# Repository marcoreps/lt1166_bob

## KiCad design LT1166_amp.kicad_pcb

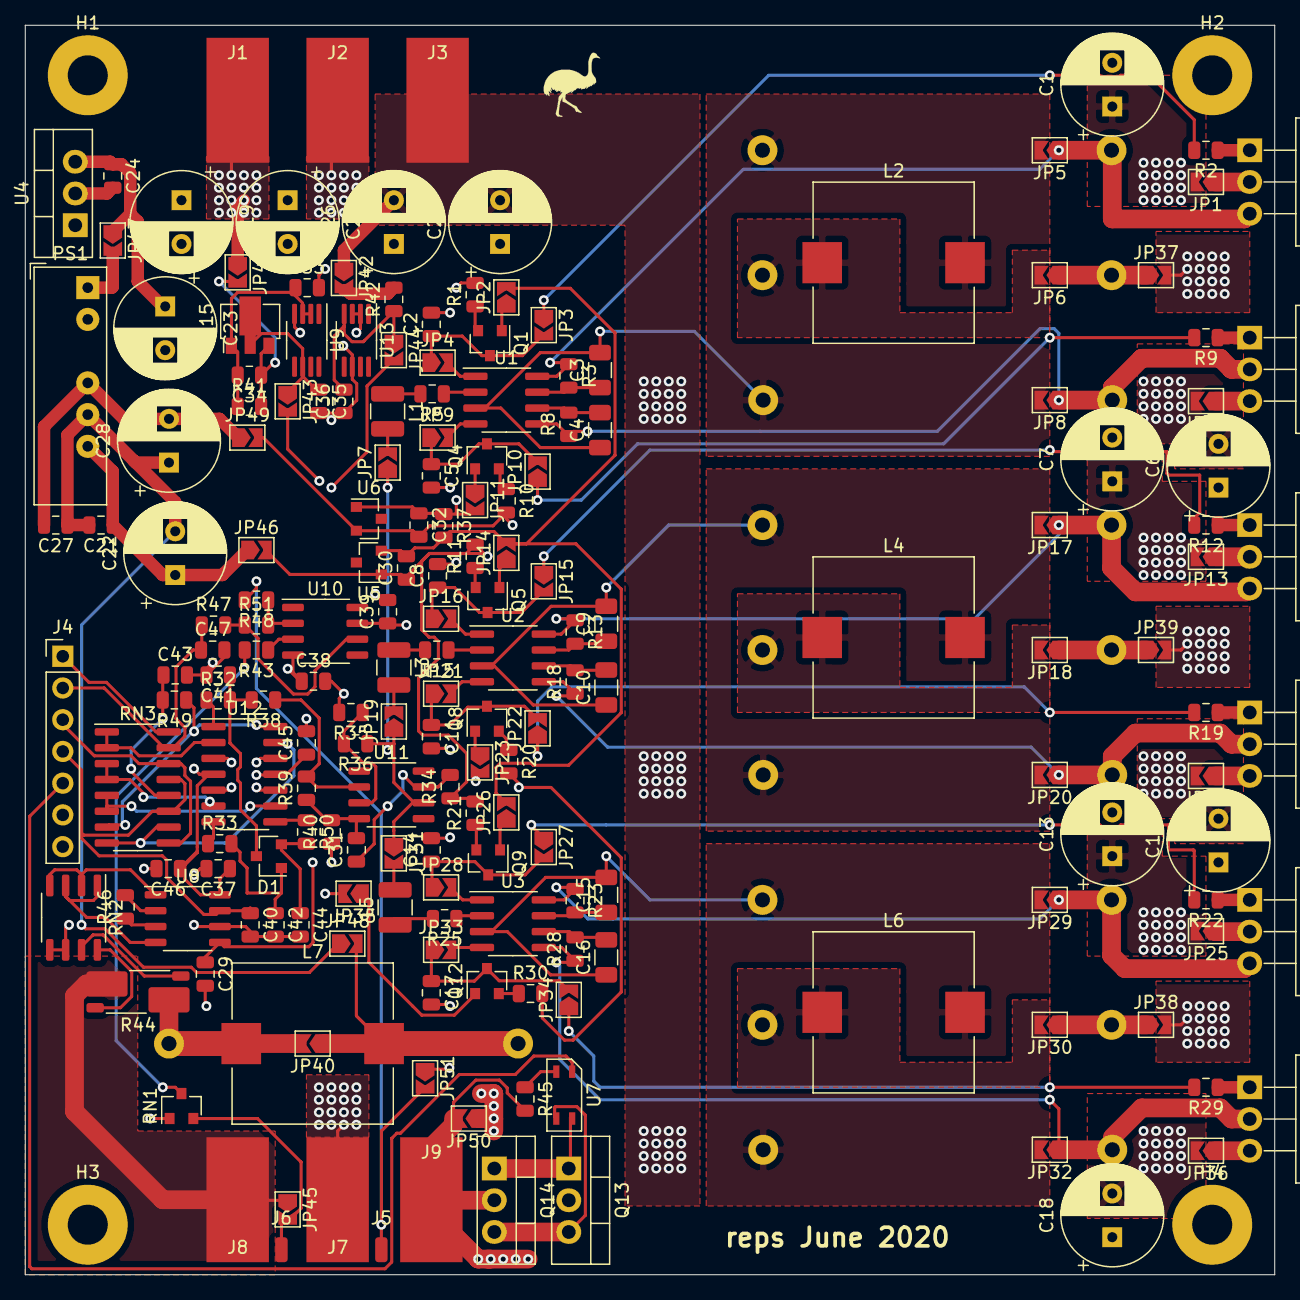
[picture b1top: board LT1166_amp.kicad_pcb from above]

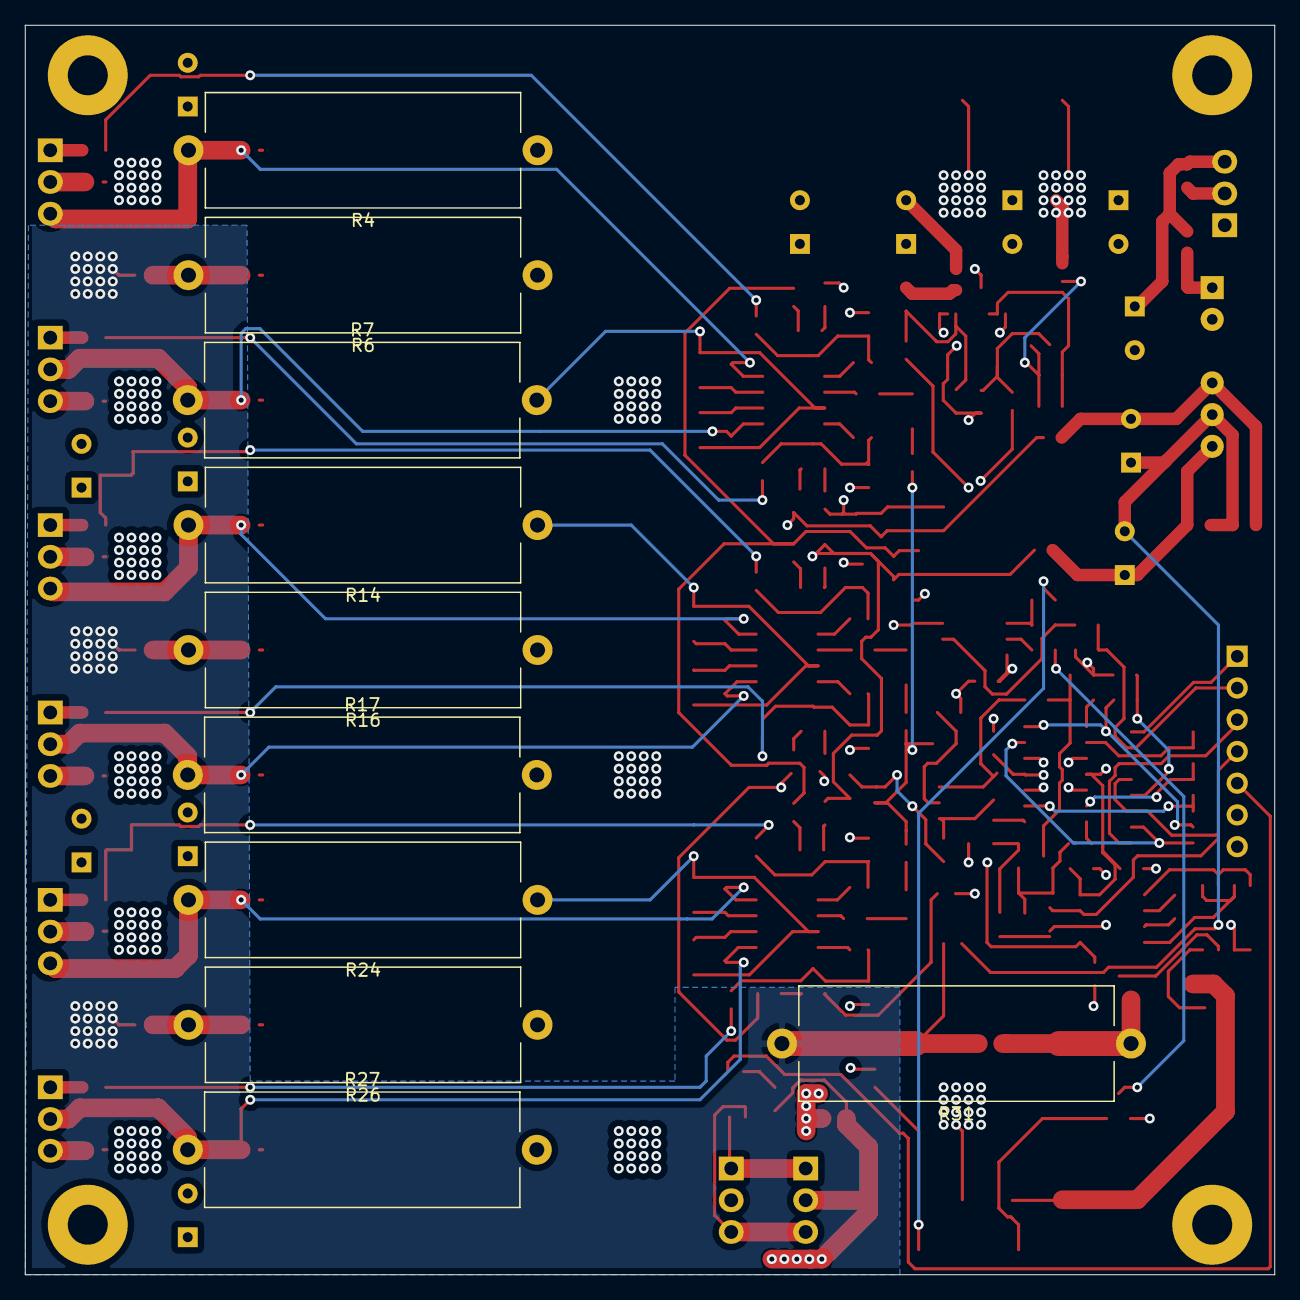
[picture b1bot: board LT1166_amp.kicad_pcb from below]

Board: 4 copper layers, 100.0 x 100.0 mm, 202 parts (10 on the bottom side), 132 nets.

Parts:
C1, C6, C7, C12, C13, C18, C19, C20, C25, C26: 1000µF; CP_Radial_D8.0mm_P3.50mm
C2, C5, C8, C11, C14, C17: 1nF; C_0805_2012Metric
C3, C4, C9, C10, C15, C16: 1µF; C_1206_3216Metric
C21, C24, C27, C29, C31, C33, C37, C38, C39, C45, C46: 100nF; C_0805_2012Metric
C22, C23, C28: 220µF; CP_Radial_D8.0mm_P3.50mm
C30, C32: 10µF; C_0805_2012Metric
C34: 4.7µF; C_0805_2012Metric
C35, C36: 1µF; C_0805_2012Metric
C40, C41, C42, C43, C44, C47: 0nF; C_0805_2012Metric
D1: D_Schottky_x2_Serial_AKC; SOT-23
H1, H2, H3, H4: MountingHole_Pad; MountingHole_3.2mm_M3_Pad
J1, J2, J3: Conn_01x01; SolderWirePad_1x01_SMD_5x10mm
J4: Conn_01x07; PinHeader_1x07_P2.54mm_Vertical
J5: sense-r; SolderWirePad_1x01_SMD_1x2mm
J6: sense-f; SolderWirePad_1x01_SMD_1x2mm
J7: return; SolderWirePad_1x01_SMD_5x10mm
J8: force; SolderWirePad_1x01_SMD_5x10mm
J9: PE; SolderWirePad_1x01_SMD_5x10mm
JP1, JP2, JP3, JP4, JP5, JP6, JP7, JP8, JP9, JP10, JP11, JP12, JP13, JP14, JP15, JP16, JP17, JP18, JP19, JP20, JP21, JP22, JP23, JP24, JP25, JP26, JP27, JP28, JP29, JP30, JP31, JP32, JP33, JP34, JP35, JP36, JP37, JP38, JP39, JP40, JP41, JP42, JP43, JP44, JP45, JP46, JP47, JP48, JP49, JP50, JP51: Jumper_NC_Small; SolderJumper-2_P1.3mm_Open_TrianglePad1.0x1.5mm
L1, L3, L5: 180µH; L_1210_3225Metric
L2, L4, L6: 0.4µH; L_Vishay_IHLP-5050
L7: 1.5µH; L_Vishay_IHLP-5050
PS1: IA2415S; Converter_DCDC_XP_POWER-IAxxxxS_THT
Q1, Q5, Q9: Q_PNP_BEC; SOT-23
Q2, Q6, Q10: IRF540N; TO-220-3_Horizontal_TabDown
Q3, Q7, Q11: IRF9540N; TO-220-3_Horizontal_TabDown
Q4, Q8, Q12: Q_NPN_BEC; SOT-23
Q13, Q14: Q_NMOS_GDS; TO-220-3_Vertical
Q15: Q_PNP_BCE; SOT-89-3
R1, R2, R9, R10, R11, R12, R19, R20, R21, R22, R29, R30: 100R; R_0805_2012Metric
R3, R8, R13, R18, R23, R28: 1k; R_0805_2012Metric
R4, R6, R7, R14, R16, R17, R24, R26, R27: 0.33R; R_Axial_Power_L25.0mm_W9.0mm_P27.94mm
R5, R15, R25: 2k; R_0805_2012Metric
R31: 1R; R_Axial_Power_L25.0mm_W9.0mm_P27.94mm
R32, R38: 10kOhm; R_0805_2012Metric
R33, R43, R47, R48, R49, R50, R51: 0Ohm; R_0805_2012Metric
R34, R40: 390Ohm; R_0805_2012Metric
R35: 9.1kOhm; R_0805_2012Metric
R36, R37, R39: 1kOhm; R_0805_2012Metric
R41: 220Ohm; R_0805_2012Metric
R42: 4kOhm; R_0805_2012Metric
R44: 10mOhm; R_Shunt_Vishay_WSK2512_6332Metric_T2.21mm
R45: 250Ohm; R_0805_2012Metric
R46: 316Ohm; R_0805_2012Metric
RN1: MPM; SOT-23
RN2: 10:1; SO-8_3.9x4.9mm_P1.27mm
RN3: R_Pack08_Split; SOIC-16_3.9x9.9mm_P1.27mm
U1, U2, U3: LT1166; SOIC-8_3.9x4.9mm_P1.27mm
U4: L7824; TO-220-3_Vertical
U5, U6: LM4040DBZ-2.5; SOT-23
U7: TLP3914; SSOP-4
U8: AD8429; SO-8_3.9x4.9mm_P1.27mm
U9, U13: LT6657BHMS8-5; MSOP-8_3x3mm_P0.65mm
U10, U11: LT1360; SO-8_3.9x4.9mm_P1.27mm
U12: Opamp_Quad_Generic; SOIC-14_3.9x8.7mm_P1.27mm

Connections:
+5V: C37.1, C39.1, C46.1, JP43.2, U8.8, U10.7, U12.4
+15VF: C30.1, JP46.2, R1.2, R11.2, R21.2, R34.1, U5.1
+24V: C23.1, C24.1, JP47.1, U4.3
+VDC: C1.1, C7.1, C13.1, C19.1, C20.1, J1.1, JP1.2, JP13.2, JP25.2, JP41.1, U4.1
-5V: C29.1, C38.1, C45.1, JP44.2, U8.5, U10.4, U12.11
-15VF: C32.2, JP49.2, R10.2, R20.2, R30.2, R40.1, U6.2
-VDC: C6.2, C12.2, C18.2, C25.2, C26.2, J3.1, JP12.2, JP24.2, JP36.2, JP42.1
/Output and feedback/I_fb: C40.1, J4.4, RN3.11, RN3.13, U8.7
/Output and feedback/PE_ssr: J4.5, U7.1
/Output and feedback/V_fb: C47.1, J4.2, R47.1, RN3.15
/Output and feedback/in: JP40.2, L7.1, R31.1, R44.1
/Power slice 1/in: JP7.1, JP19.1, JP31.1, R36.1, U11.6
/V I clamp/I_set: J4.3, RN3.9, RN3.14
/V I clamp/V_set: J4.1, RN3.16
GND: C1.2, C2.2, C5.2, C6.1, C7.2, C8.2, C11.2, C12.1, C13.2, C14.2, C17.2, C18.1, C19.2, C20.2, C23.2, C24.2, C25.1, C26.1, C29.2, C33.2, C35.2, C36.1, C37.2, C38.2, C39.2, C40.2, C41.2, C42.2, C43.2, C44.2, C45.2, C46.2, C47.2, J2.1, J4.6, J7.1, JP50.1, JP51.1, PS1.2, Q13.2, R35.2, RN1.1, RN2.5, RN2.6, U4.2, U8.6, U9.4, U12.3, U12.5, U12.10, U12.12, U13.2, U13.3, U13.6
unnamed: C2.1, JP3.2, JP4.1, Q1.3
unnamed: C3.1, R3.2, U1.7
unnamed: C3.2, C4.1, JP5.2, JP8.2, L2.2, R4.1, R7.2, U1.3
unnamed: C4.2, R8.2, U1.6
unnamed: C5.1, JP9.1, JP10.2, Q4.3
unnamed: C8.1, JP15.2, JP16.1, Q5.3
unnamed: C9.1, R13.2, U2.7
unnamed: C9.2, C10.1, JP17.2, JP20.2, L4.2, R14.1, R17.2, U2.3
unnamed: C10.2, R18.2, U2.6
unnamed: C11.1, JP21.1, JP22.2, Q8.3
unnamed: C14.1, JP27.2, JP28.1, Q9.3
unnamed: C15.1, R23.2, U3.7
unnamed: C15.2, C16.1, JP29.2, JP32.2, L6.2, R24.1, R27.2, U3.3
unnamed: C16.2, R28.2, U3.6
unnamed: C17.1, JP33.1, JP34.2, Q12.3
unnamed: C21.1, C22.1, JP46.1, PS1.6
unnamed: C21.2, C22.2, C27.1, C28.1, JP48.1, PS1.5
unnamed: C27.2, C28.2, JP49.1, PS1.4
unnamed: C31.1, R34.2, U11.7
unnamed: C31.2, R39.1, R40.2, U11.4
unnamed: C33.1, C34.2, Q15.1, R41.1, U9.2, U9.3
unnamed: C34.1, JP41.2, Q15.3, R41.2
unnamed: C35.1, JP43.1, Q15.2, U9.6
unnamed: C36.2, JP44.1, R42.1, U13.4
unnamed: C42.1, D1.1, R33.2
unnamed: C43.1, R49.2, RN3.12
unnamed: C44.1, D1.2, R50.2
unnamed: J5.1, JP51.2, R48.2
unnamed: J6.1, JP45.2, RN1.2
unnamed: J8.1, JP45.1, R44.4
unnamed: JP1.1, Q2.2
unnamed: JP2.1, Q1.1
unnamed: JP3.1, R2.2
unnamed: JP4.2, U1.1
unnamed: JP5.1, Q2.3, R3.1, R4.2, U1.8
unnamed: JP6.2, L2.1, R6.1
unnamed: JP7.2, L1.2
unnamed: JP8.1, Q3.2, R7.1, R8.1, U1.5
unnamed: JP9.2, U1.4
unnamed: JP10.1, R9.2
unnamed: JP11.1, Q4.1
unnamed: JP12.1, Q3.3
unnamed: JP13.1, Q6.2
unnamed: JP14.1, Q5.1
unnamed: JP15.1, R12.2
unnamed: JP16.2, U2.1
unnamed: JP17.1, Q6.3, R13.1, R14.2, U2.8
unnamed: JP18.1, JP39.1, R16.2
unnamed: JP18.2, L4.1, R16.1
unnamed: JP19.2, L3.2
unnamed: JP20.1, Q7.2, R17.1, R18.1, U2.5
unnamed: JP21.2, U2.4
unnamed: JP22.1, R19.2
unnamed: JP23.1, Q8.1
unnamed: JP24.1, Q7.3
unnamed: JP25.1, Q10.2
unnamed: JP26.1, Q9.1
unnamed: JP27.1, R22.2
unnamed: JP28.2, U3.1
unnamed: JP29.1, Q10.3, R23.1, R24.2, U3.8
unnamed: JP30.1, JP38.1, R26.2
unnamed: JP30.2, L6.1, R26.1
unnamed: JP31.2, L5.2
unnamed: JP32.1, Q11.2, R27.1, R28.1, U3.5
unnamed: JP33.2, U3.4
unnamed: JP34.1, R29.2
unnamed: JP35.1, Q12.1
unnamed: JP36.1, Q11.3
unnamed: JP6.1, JP37.1, R6.2
unnamed: JP42.2, R42.2
unnamed: JP47.2, PS1.1
unnamed: L1.1, R5.2
unnamed: L3.1, R15.2
unnamed: L5.1, R25.2
unnamed: Q1.2, R1.1
unnamed: Q2.1, R2.1
unnamed: Q3.1, R9.1
unnamed: Q4.2, R10.1
unnamed: Q5.2, R11.1
unnamed: Q6.1, R12.1
unnamed: Q7.1, R19.1
unnamed: Q8.2, R20.1
unnamed: Q9.2, R21.1
unnamed: Q10.1, R22.1
unnamed: Q11.1, R29.1
unnamed: Q12.2, R30.1
unnamed: Q13.1, Q14.1, U7.4
unnamed: Q13.3, Q14.3, U7.3
unnamed: R5.1, U1.2
unnamed: R15.1, U2.2
unnamed: R25.1, U3.2
unnamed: R32.1, U12.1
unnamed: R33.1, U12.7
unnamed: R35.1, R36.2, U11.3
unnamed: R38.1, R39.2, U11.2
unnamed: R43.1, U10.3
unnamed: R43.2, RN1.3
unnamed: R44.2, RN2.7
unnamed: R44.3, RN2.8
unnamed: R45.1, U7.2
unnamed: R46.1, U8.3
unnamed: R46.2, U8.2
unnamed: R47.2, R51.1, U10.6
unnamed: R48.1, R51.2, U10.2
unnamed: R49.1, RN3.7, U12.14
unnamed: R50.1, U12.8
unnamed: RN2.1, RN2.3, U8.4
unnamed: RN2.2, RN2.4, U8.1
unnamed: RN3.1, RN3.2, U12.2
unnamed: RN3.3, RN3.4, U12.6
unnamed: RN3.5, RN3.6, U12.9
unnamed: RN3.8, RN3.10, U12.13
PE: H1.1, H2.1, H3.1, H4.1, J4.7, J9.1, JP50.2, Q14.2, R45.2
bot_drive: C32.1, JP11.2, JP23.2, JP35.2, R37.1, U6.1
pwr_ctrl: C41.1, D1.3, R32.2, R38.2
pwr_out: JP37.2, JP38.2, JP39.2, JP40.1, JP48.2, L7.2, R31.2
top_drive: C30.2, JP2.2, JP14.2, JP26.2, R37.2, U5.2
